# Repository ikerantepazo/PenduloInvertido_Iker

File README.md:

# PenduloInvertido_Iker
En este repositorio se encuentra tanto la práctica 4 cómo la práctica 6 de la asignatura de Teoría de Control

PRÁCTICA 4 - *PID en tiempo discreto*

Esta práctica tiene como objetivo implementar una biblioteca de controladores PID en tiempo discreto para ser utilizada en un microcontrolador ESP32, con aplicación directa en el control de un péndulo invertido. Esta biblioteca será utilizada en el desarrollo del proyecto de control descrito en el capítulo 6 del guión de prácticas.

Se desarrollarán tres variantes del controlador PID en tiempo discreto:

-PID : utiliza aproximaciones hacia atrás para las derivadas y sumas acumulativas para la integral.
-PID como filtro IIR: modelado mediante transformada Z, facilitando su implementación como filtro digital.
-PID filtro baja : se le pone un filtro al término derivativo para evitar que el ruido o los cambios bruscos del error afecten al control.

Cada implementación está basada en los pseudocódigos del guión.

Esta práctica está encapsulada en la carpeta libraries donde nos encontraremos :

I2Cdev/

Contiene archivos fuente y cabeceras que permiten la comunicación mediante el protocolo I2C. Es una biblioteca comúnmente usada para facilitar la lectura y escritura con sensores como el MPU6050

MPU6050/

Incluye las definiciones y funciones específicas para el sensor MPU6050, que proporciona mediciones de aceleración y giroscopio. Esta biblioteca se apoya en I2Cdev para obtener los datos del sensor y es esencial para calcular la posición y velocidad angular del péndulo.

PIDController/

Es la biblioteca desarrollada para está práctica para implementar los tres tipos de controladores PID discretos:

-PID directo
-PID como filtro IIR
-PID filtro pasa baja

Dentro de cada carpeta estarán los archivos .h y .cpp con la implementación de las clases PID

Se añadirá además una carpeta examples que contendrá tres ejemplos simples que muestran cómo usar cada una de las variantes del controlador PID implementadas.

CodigoCompletoPendulo.ino

Este es el sketch código principal de Arduino que integra las bibliotecas anteriores. Aquí se encuentra el código de control que:

-Lee el ángulo del péndulo usando el MPU6050
-Calcula la señal de control con el PID
-Aplica la corrección al actuador
-Permite probar y comparar las distintas variantes del controlador PID

PRÁCTICA 6 - **PENDULO INVERTIDO**

Iker Antepazo Cancelas 

**Introducción:**
**\
` `En este documento recogeremos el proceso llevado a cabo para la creación y construcción de un robot llamado “péndulo invertido”, cuya función será de tratar de mantenerse en posición vertical con una tolerancia de ±5◦. 

El sistema debe compensar los empujones externos y volver a la posición vertical y debe ser capaz de poder iniciar su funcionamiento desde cualquier posición. 

**Metodología seguida**

1. **Buscar proyectos similares:** Investigar si ya existe un proyecto de un robot similar que sea funcional y esté documentado. Tanto en respositorios de github como en mi caso en videos de la plataforma YouTube y en la página “grabcad”. 
1. **Investigación general:** Como no existe ningún proyecto bien hecho y bien documentado que esté completo, procedemos a investigar el modus operandi que trataremos de llevar a cabo el proyecto partiendo de las ideas que sacamos de los sitios web antes mencionados. 
3. **Fijación de objetivos:** Es importante la fijación de ciertas metas para saber qué hardware necesitamos. Tanto es así para nuestro chasis como para nuestra placa PCB. 
3. **Selección del Hardware:** Una vez que sabemos las metas que queremos lograr conseguir con nuestro robot, tenemos que buscar el hardware necesario que se adapte a la perfección con lo que necesitaremos. 
3. **Diseño de la PCB:** Deberemos crear desde 0 una placa PCB diseñada por KiCad que contenga los elementos que emplearemos para el robot y las pistas con los mismos elementos conectados entre sí a través de los pines. 
3. **Diseño del Chasis:** Deberemos resolver dos problemáticas: tener el peso compensado y tener el centro de gravedad bajo. 
3. **Prueba de componentes por separado:** Verificamos que todo funcione por separado para luego soldar todo en la placa. 
3. **Montaje:** Montamos todos los componentes en el chasis para poder probar el robot al completo. 
3. **Programación inicial:** Hacemos un primer código que solo mantenga el robot estático en un mismo lugar. 
3. **Ajuste del PID:** Ajustamos los valores del PID para que el robot se mantenga estático. 

**Objetivos**

**Estabilidad Perpendicular al Suelo:**  

Garantizar que el robot sea capaz de mantenerse estable en la posición perpendicular al suelo (vertical). ✔ 

**Compensación de Empujones:**  

Desarrollar la capacidad del robot para compensar empujones y así evitar las caídas. ✔ 

**Arranque desde Cualquier Posición:** Lograr que el robot pueda iniciar su funcionamiento desde cualquier posición inicial. ✔ 

**Reducción de Posibilidades de Volcar:** Minimizar las posibilidades de que el robot vuelque y se caiga y asegurar que el robot no pueda volver a una posición no deseada. ✔ 

**Investigación** 

En relación con la búsqueda de otros proyectos de este estilo, he detectado una problemática: hay varios proyectos hechos con el mismo principio, pero nadie ha creado una documentación completa y descriptiva del proyecto, esto conlleva a un mayor gasto y empleo de tiempo en la búsqueda de los elementos hardware que debemos comprar y buscar, al igual que para el desarrollo de la pcb empleada y del diseño del chasis. En parte tuve suerte ya que gracias a toda la información recopilada por las páginas web y gracias al trabajo del compañero Daniel Acevedo, que fue el primero en hacer este proyecto y gracias al cual he sacado adelante este robot. Aunque hay esta escasez de información, he podido rescatar algo de información examinando videos. De ellos, he determinado el hardware que se necesita y el tipo de control para manejar el movimiento (PID). 

**Hardware** 

Para la selección del hardware, se buscó que el robot se hiciera con elementos básicos y comunes para que sea un robot de bajo costo y no dependa de cierta solvencia para poder realizarse, ya que como no hay verdaderamente un informe completo y descriptivo de todos los pasos a seguir podría atascarse el proyecto y ser necesarias varias pruebas como fue mi caso. 

**ESP32:**  

Para el microcontrolador, he empleado una ESP32. En concreto, se ha utilizado una ESP32 que ronda los 11€ en Amazon. He consultado un par de páginas web para informarme al respecto de esta placa, y a continuación dejaré todo lo necesario a conocer sobre esta placa:[ ESP32 ](https://es.wikipedia.org/wiki/ESP32). 

Este elemento es el encargado de mediante una conexión con cable USB al ordenador en la aplicación de Arduino, recibir los programas empleados. 

**MPU-6050:**  

Este sensor tiene incorporado un acelerómetro y un giroscopio, los cuales vamos a usar para medir la orientación e inclinación del robot, que como hemos comentado al principio del documento buscamos que pueda mantener la verticalidad sin sobrepasar los 5 grados de inclinación angular. Las fórmulas e información necesaria que he necesitado para usar este sensor están en esta página web:[ MPU6050 ](https://invensense.tdk.com/wp-content/uploads/2015/02/MPU-6000-Datasheet1.pdf). 

En el caso de este componente tuve serios problemas para encontrarlo ya que lo compré tres veces, pero me daba errores al probarlo hasta que acabé encontrando el idóneo. 

**Condensadores:**  

Empleé dos condensadores, uno de 0.1 uF y otro de 0.22uF:[ 0,1uF ](https://www.microjpm.com/products/capacitor-electrolitico-0-1uf-50v/)[,0,22uF ](https://www.microjpm.com/products/capacitor-electrolitico-50v-0-22uf/)

**Bloques terminales:** 

En este aspecto emplee tres bloques terminales que fueron los encargados de conectarse con los motores y la batería. A continuación, dejaré un enlace para el acceso a sus características:[ Bloques terminales ](https://es.rs-online.com/web/b/wurth-elektronik/conectores/bloques-terminales/?displayMonolithBrandPage=true)

**TB6612FNG:**  

El driver que he elegido es una solución más moderna que el común puente H; su precio es de menos de 2€ y nos permite controlar 2 motores simultáneamente y de manera independiente. He seleccionado este componente al igual que los demás gracias a la documentación presentada por Daniel Acevedo. Al igual que con el anterior sensor, la página de la que extraje toda la información la dejo en el siguiente enlace:[ TB6612FNG ](https://cdn.sparkfun.com/assets/0/1/b/b/3/TB6612FNG.pdf)

**Batería:** En este aspecto he empleado un portapilas de 4 pilas AA conectadas a los bornes de la placa.[ Portapilas AA ](https://www.amazon.es/CABLEPELADO-Portapilas-Interruptor-Soporte-Bater%C3%ADa/dp/B0B8VN7ZGZ/ref=sr_1_2_sspa?adgrpid=59855380287&dib=eyJ2IjoiMSJ9.0E4CYsIV8j7auTO14bG8hEXhwvBaReMFm0fjOPfJ3q8TX14t1DLaU0U6P-UUNUNhfeTnEdwRfe7vn24negRVgewhSJFmLo8vVjgERoEZWngb98hE1KTaQ585Hpb3RDzaZIQ5MAbn2fep-qAn-dRbsQS6pKlv9gUcdxg1BLczaTV1ES7gaFhVuajTCM7wP9TMQYEPgGFh99MIJ9aMC1JcNtHe7sM8db4In1UUd3a5C00RE-3oAFUU7VeJgylTTtVf4uSGRtyNm3ea7Xobz3k4uEAb4xq73gyJuEwPlg-UE9s.VIBVw3cz8qMJSTzGRXrtYivpHGLmTSzFw5oaB0C6DoU&dib_tag=se&hvadid=712269289876&hvdev=c&hvexpln=0&hvlocphy=9217726&hvnetw=g&hvocijid=354578821341335653--&hvqmt=b&hvrand=354578821341335653&hvtargid=kwd-368883696421&hydadcr=3445_2435935&keywords=portapila%2Baa&mcid=e65aab6caa613c229322b2821ad0fe45&qid=1749406825&sr=8-2-spons&sp_csd=d2lkZ2V0TmFtZT1zcF9hdGY&th=1)

**Motores y ruedas:**  

En este proyecto se han usado los comúnmente usados motores de DC con una reductora, la cual permite un fácil acople de una rueda que normalmente se vende con el propio motor.[ Motores y ruedas ](https://www.amazon.es/Gebildet-Motorreductor-Tracci%C3%B3n-Rob%C3%B3tico-Neum%C3%A1tico/dp/B08D39MFN1/ref=sr_1_1?__mk_es_ES=%C3%85M%C3%85%C5%BD%C3%95%C3%91&crid=1P1HI1AFTWELM&dib=eyJ2IjoiMSJ9.HRliVdVUooMfJ37_hB8r_pSJvEV5XNTqh8w4QUlMzPO8MLZGwhfzxdawege97K2pqwPePnT-DpDTJWyFgOl3We7KRaOzLvQuHXiuwfkcSI4S0dd1IR4lIPmYOkRhYtcfeCPd7Voi_DjQLjdWadgksw2yd01QWSmv9UIRkRiq65oQbt6oqpc5atx7QseQLc1OS11eH21BWngueKm1hwkIQ4lZicSd-Uhgugbw9jDTS-GnUuf1Kxd1msYV32x-stqU7vNEJ1KQYF6bO2tZLm_0Cfw12w8KJTQMtQ0VRDSMzLk.xFuda1aL2pKo9rfUjou-0chu3DpncL0IzS-mdohaGTc&dib_tag=se&keywords=ruedas%2Brobot&qid=1749406908&sprefix=ruedas%2Brobot%2Caps%2C167&sr=8-1&th=1) 

**Regulador de voltaje:** 

En este aspecto emplee un regulador de voltaje LM7805 que me servirá para 

controlar el flujo de voltaje en el circuito. Aquí dejaré una datasheet para  comprender su funcionamiento y características:[ Regulador de voltaje ](https://www.alldatasheet.com/view.jsp?Searchword=Lm7805%20datasheet&gad_source=1&gad_campaignid=1421144141&gclid=CjwKCAjw6ZTCBhBOEiwAqfwJd2oRRv3XeQ9ZCx_5SY_imFatNLl_RGne5QrWJkQlLroW2QNfGPGR_hoC_5wQAvD_BwE)

**PCB** 

He diseñado una placa PCB capaz de emplear todos los elementos antes  

mencionados y que estén conectados entre sí de forma que nos funcione todo a   la perfección. En este aspecto debemos buscar la obtención de una placa que   no tenga mucho lío de pistas para ver la función de cada una de ellas a la   perfección, buscamos una claridad importante para en caso de alguna duda  presentada a la hora de la soldadura de los elementos con el estañador saber de   qué pin a qué otro pin va cada pista. 

Asímismo es de vital importancia el contar con una placa de pocas  

dismensiones para así facilitarnos el proceso de creación del chasis, porque no   queremos un robot muy grande, con lo cual esto será muy importante. 

**Chasis**

He diseñado 2 tipos de chasis para el robot el primero fue para tantear más o menos, y con el segundo, gracias a los consejos de Daniel he logrado hacer funcionar el robot ya que cumple correctamente con los requisitos del centro del centro de gravedad que estaba muy centrado y a una altura baja, lo que proporcionaba una gran estabilidad.  

Lo importante a tener en cuenta para el desarrollo del chasis son los siguientes dos requisitos: 

**Centro de gravedad:** Es determinante que el centro de gravedad del robot sea el más bajo posible. Si el peso está muy elevado respecto al suelo, se hará prácticamente imposible que el robot sea capaz de mantenerse derecho. 

**Peso centrado:** Al igual que el centro de gravedad bajo, es decisivo que el peso del robot esté centrado en el eje de las ruedas, lo que hará que, combinado con el apartado anterior, el robot debería mantenerse en la posición que queremos sin necesidad de que el robot esté encendido. Cuanto más estable sea el robot gracias al diseño del chasis, más sencillo nos será ajustar el PID hasta lograr que el robot funcione correctamente. Ahora voy a explicar los problemas de mis distintos chasis hasta el momento en que fui capaz de hacer que el robot funcionara. 

***Primer chasis:*** 

Después de corregir los errores de los dos chasis mencionados por Daniel Acevedo en su documentación, logré hacer un chasis con el que robot funcionara. En este caso, el centro de gravedad estaba muy centrado y a una altura baja, lo que proporcionaba una gran estabilidad incluso cuando el robot estaba apagado. Pero no se adaptaba completamente con mis necesidades debido al uso de los motores antes mencionados. 

Este primer chasis lo he desarrollado a través de la página web de ”onshape” lo que me permitió diseñar incluso el portapilas pero se me hizo muy duro y difícil terminar con este proceso con lo cual para el segundo chasis me pasé a FreeCad. 

***Segundo chasis:*** 

Este segundo chasis lo he diseñado con la ayuda de FreeCad, le he agregado   calculando las dimensiones de la placa PCB unos agujeros para permitirnos   atornillar la placa al chasis con tuercas y tornillos asegurándonos así la fijación   de esta. Al igual que esta novedad también le he agregado unas elevaciones en   los laterales de la placa para poder atornillar nuestros motores en posición    vertical permitiéndonos de este modo emplear los motores tradicionales antes  mencionados. 

Este fue el diseño final del chasis ya que se adaptaba a la perfección con lo  

deseado, con lo cual generamos el archivo .gcode para enviar a la impresora 3d.   Esto se hizo gracias a la aplicación Ultimaker Cura. 

A partir de aquí la impresión duró 4 horas aproximadamente, pero tuve  bastantes problemas con las impresoras del centro debido a que se quedaba atascado el material y había ciertos errores de calibración en la impresora 

empleada. 

**Prueba de componentes por separado** 

**MPU-6050:** 

Realizamos una primera prueba para verificar que el sensor funcione 

Como vemos que el sensor nos proporciona medidas coherentes, procedemos  a calibrar el sensor en la posición en la que estará midiendo. 

Finalmente, probamos el código que utilizaremos para medir el ángulo de 

inclinación del robot. 

TB6612FNG: 

Al igual que los códigos del sensor anterior, los he modificado antes de subirlos   a la ESP32, ajustando los pines para que sean compatibles con la ESP32: 

**Montaje** 

El montaje es muy simple, debemos conectar todo de la manera en la que hemos diseñado la PCB. Además de las conexiones de los sensores, 

necesitamos alimentar los motores y la ESP32.  Ambos trabajan a voltajes   distintos, por lo que requerimos un regulador de voltaje. Los motores los he   alimentado a 9V, y la ESP32 se alimenta a 5V en el pin 5V.  

**Ajuste del PID** 

Para poder ajustar el PID, es necesario comprender la función de cada una de   las tres componentes de este sistema de control. 

**Empezar desde 0:** 

Es crucial comenzar con todos los valores desde 0 y ajustar los valores de 

manera ordenada e independiente. 

**Orden de calibración:** 

Se recomienda iniciar ajustando los valores de Kp hasta lograr que el robot sea   capaz de levantarse desde el suelo. Una vez logrado esto, se anota el valor optimo y se establece la variable a 0. 

Luego, se ajusta Kd, buscando un valor en el cual el robot no oscile  exageradamente y casi se mantenga en la posición deseada. 

En el tercer paso, se restablece Kp al valor anotado anteriormente y se deja Kd   en el valor optimo encontrado. En este punto, Ki aun se mantiene en 0, pero primero se verifica que el robot casi se mantenga en la posición 

deseada. 

Finalmente, se ajusta Ki. Esta componente solo ayuda al robot a alcanzar la posición precisa, si las otras dos componentes no se han ajustado 

correctamente, Ki no cambiara radicalmente el comportamiento del robot. En   resumen, Kp y Ki son las más importantes. 

**Valores pequeños:** 

Los valores del PID dependen en gran medida de la construcción del robot. Es   importante tener en cuenta que cuanto mayores sean los valores, más agresivo   será el movimiento del robot. Se 

recomienda comenzar con valores menores a 1 y realizar incrementos pequeños   para evitar que 

el robot se mueva bruscamente. 

**Programación inicial** 

Al combinar los códigos previamente agregados a esta documentación con un   control PID, podemos lograr que el robot funcione. Sin embargo, es necesario 

ajustar los valores del PID para que se adapten a nuestro caso específico. 

En este punto fue donde en mi caso el robot dejó de funcionar, esto debido a que   debe haber alguna conexión en la placa que hace que la ESP32 se quede 

congelada y no acabe de enviar el programa el componente pertinente. Trataré   de solucionar este problema más adelante por mi cuenta, pero debido al cierre   de actas cercano aquí es dónde me he quedado. 

El código que deberíamos emplear sería: 

--------------------> (Está completo y descriptivo en el pdf)

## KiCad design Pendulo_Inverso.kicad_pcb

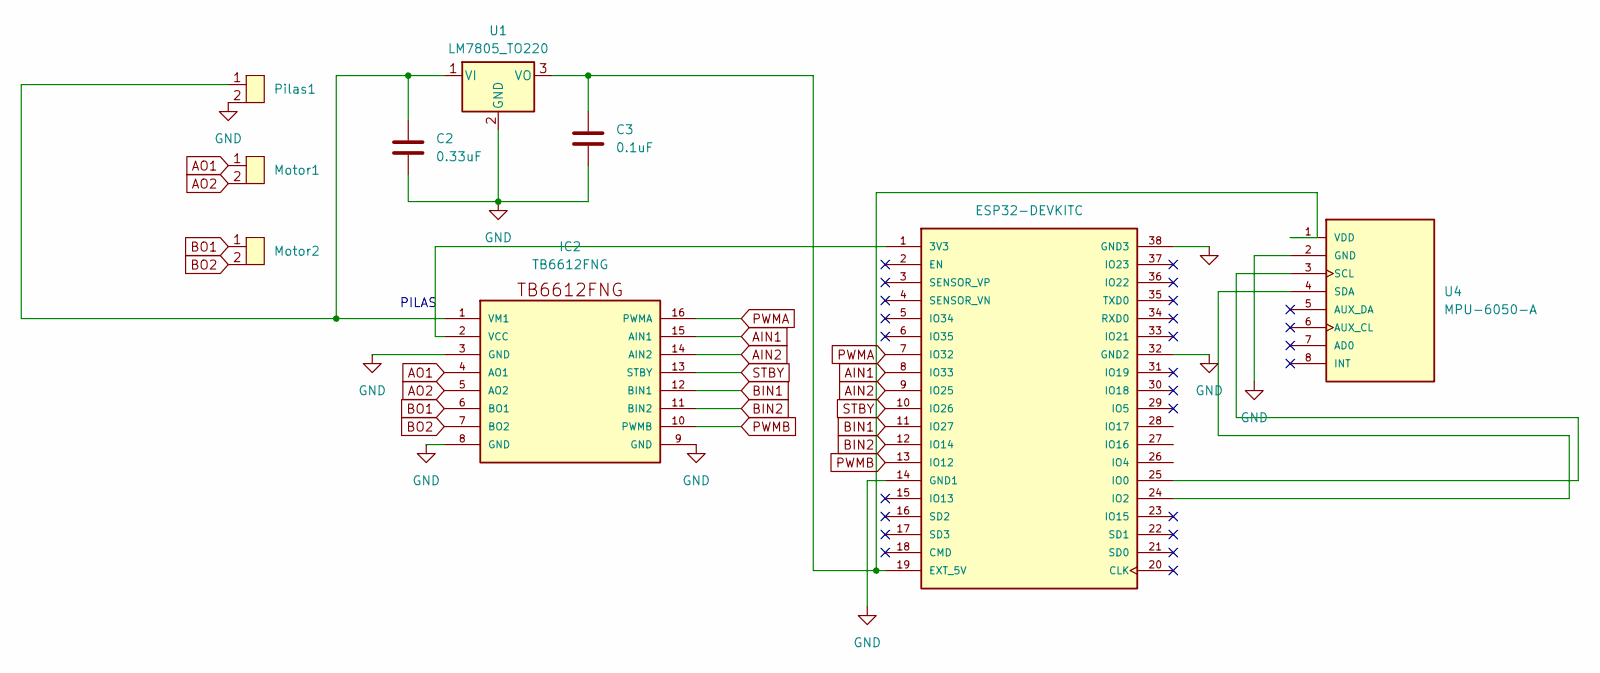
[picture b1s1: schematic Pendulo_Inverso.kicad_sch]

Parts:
C2: 0.33uF; CP_Radial_D8.0mm_P3.50mm
C3: 0.1uF; CP_Radial_D8.0mm_P3.50mm
IC2: TB6612FNG; TB6612FngSparkfun
Motor1, Motor2: TerminalBlock_Phoenix_MKDS-1,5-2_1x02_P5.00mm_Horizontal
Pilas1: TerminalBlock_Phoenix_MKDS-1,5-2_1x02_P5.00mm_Horizontal
U1: LM7805_TO220; TO-220-3_Vertical
U2: ESP32-DEVKITC; MODULE_ESP32-DEVKITC; PARTREV N/A
U4: MPU-6050-A; MPU6050; PARTREV 3.4

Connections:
AIN1: IC2.15 (AIN1), U2.8 (IO33)
AIN2: IC2.14 (AIN2), U2.9 (IO25)
AO1: IC2.4 (AO1), Motor1.1
AO2: IC2.5 (AO2), Motor1.2
BIN1: IC2.12 (BIN1), U2.11 (IO27)
BIN2: IC2.11 (BIN2), U2.12 (IO14)
BO1: IC2.6 (BO1), Motor2.1
BO2: IC2.7 (BO2), Motor2.2
GND: C2.2, C3.2, IC2.3 (GND), IC2.8 (GND), IC2.9 (GND), Pilas1.2, U1.2 (GND), U2.14 (GND1), U2.32 (GND2), U2.38 (GND3), U4.2 (GND)
unnamed: IC2.2 (VCC), U2.1 (3V3)
unnamed: C2.1, IC2.1 (VM1), Pilas1.1, U1.1 (VI)
unnamed: C3.1, U1.3 (VO), U2.19 (EXT_5V), U4.1 (VDD)
unnamed: U2.25 (IO0), U4.3 (SCL)
unnamed: U2.24 (IO2), U4.4 (SDA)
PWMA: IC2.16 (PWMA), U2.7 (IO32)
PWMB: IC2.10 (PWMB), U2.13 (IO12)
STBY: IC2.13 (STBY), U2.10 (IO26)

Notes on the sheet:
PILAS

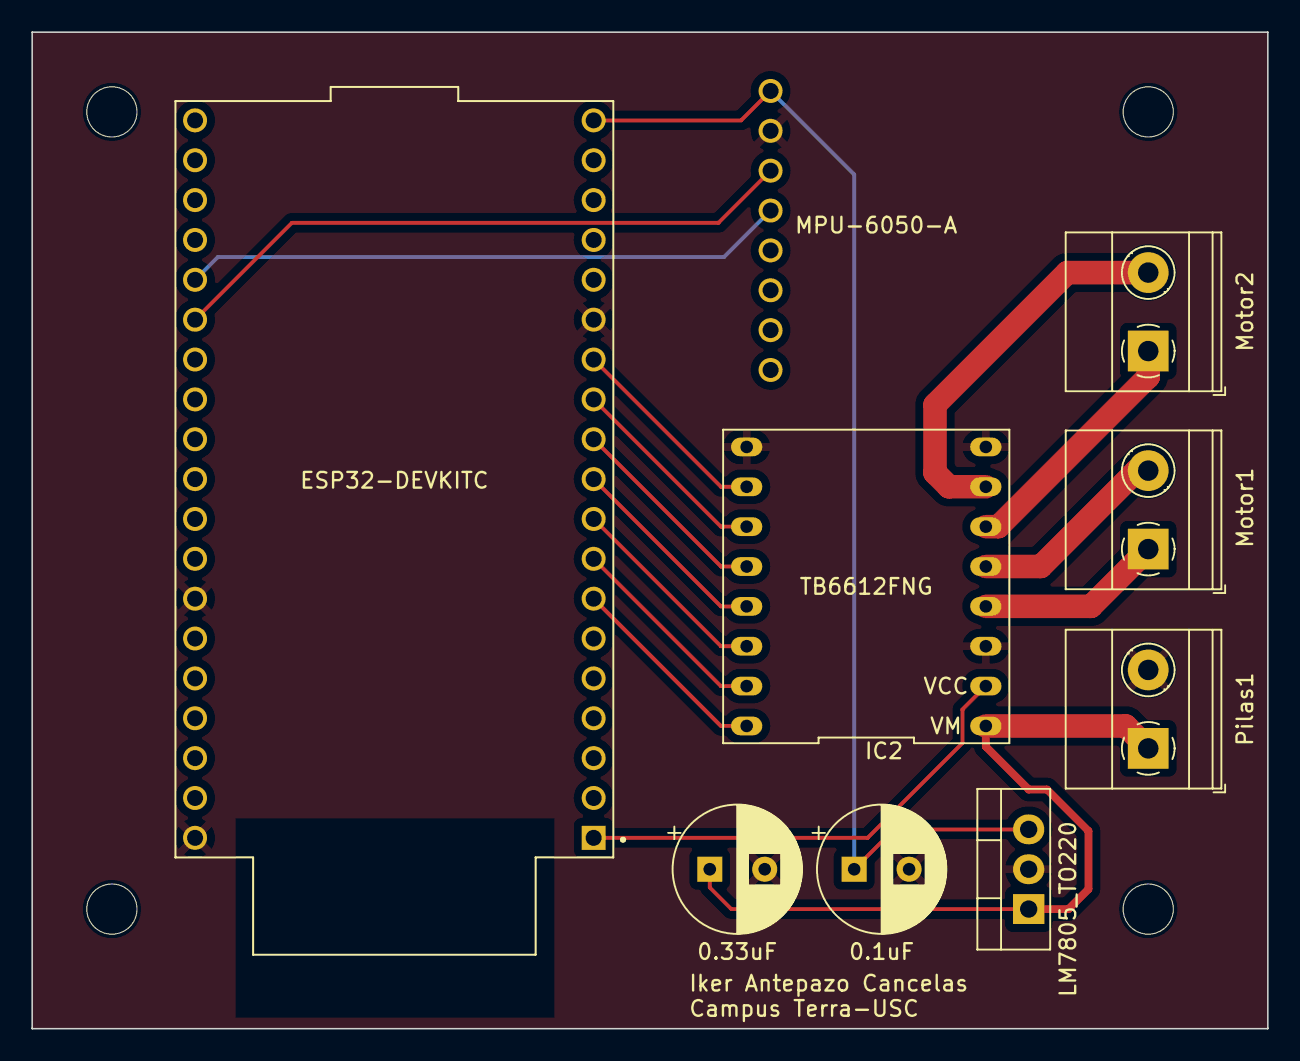
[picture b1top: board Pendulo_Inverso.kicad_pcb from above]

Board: 2 copper layers, 78.7 x 63.5 mm, 9 parts (0 on the bottom side), 17 nets.
